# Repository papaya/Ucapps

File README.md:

# Ucapps
 Midibox files PCB kicad

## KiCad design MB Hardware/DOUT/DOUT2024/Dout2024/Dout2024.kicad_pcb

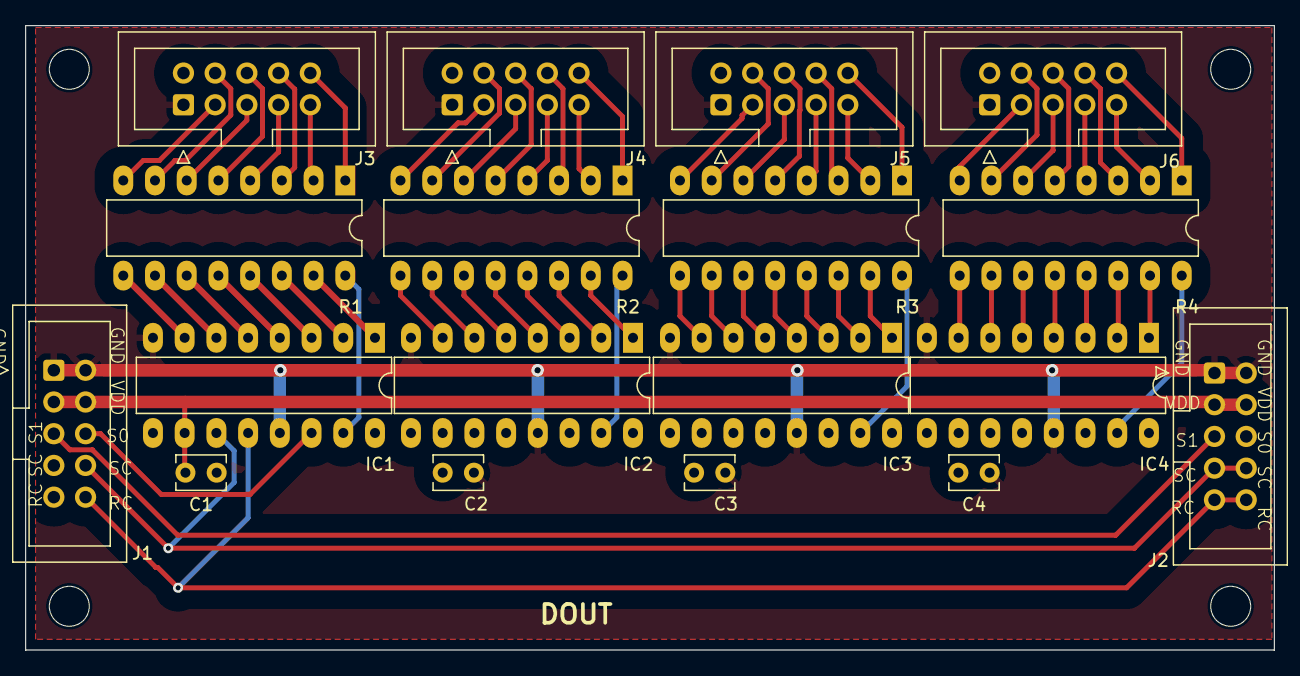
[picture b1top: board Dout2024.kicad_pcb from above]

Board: 2 copper layers, 100.0 x 50.0 mm, 22 parts (0 on the bottom side), 74 nets.

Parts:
C1, C2, C3, C4: 100NF; C_Disc_D3.8mm_W2.6mm_P2.50mm
H1, H2, H3, H4: MountingHole; MountingHole_3.2mm_M3
IC1, IC2, IC3, IC4: SN74HC595N; DIP-16_74h595
J1, J2: sin_in; IDC-Header_2x05_P2.54mm_Vertical_ksr_TO_J8_J9
J3, J4, J5, J6: sin_in; IDC-Header_2x05_P2.54mm_Vertical
R1: 220 ohm; DIP-16_R220_network
R2, R3, R4: 220 ohm; DIP-16_W7.62mm_LongPads

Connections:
+5V: C1.2, C2.2, C3.2, C4.2, IC1.10 (~SRCLR), IC1.16 (VCC), IC2.10 (~SRCLR), IC2.16 (VCC), IC3.10 (~SRCLR), IC3.16 (VCC), IC4.10 (~SRCLR), IC4.16 (VCC), J1.3, J1.4, J2.3, J2.4
/DOUT_RC: IC1.12 (RCLK), IC2.12 (RCLK), IC3.12 (RCLK), IC4.12 (RCLK), J1.10, J2.9, J2.10
/DOUT_SC: IC1.11 (SRCLK), IC2.11 (SRCLK), IC3.11 (SRCLK), IC4.11 (SRCLK), J1.8, J2.7, J2.8
/S0: IC1.14 (SER), J1.6
GND: C1.1, C2.1, C3.1, C4.1, IC1.8 (GND), IC1.13 (~OE), IC2.8 (GND), IC2.13 (~OE), IC3.8 (GND), IC3.13 (~OE), IC4.8 (GND), IC4.13 (~OE), J1.1, J1.2, J2.1, J2.2, J3.1, J4.1, J5.1, J6.1
unnamed: IC1.15 (QA), R1.16 (R1.2)
unnamed: IC1.1 (QB), R1.15 (R2.2)
unnamed: IC1.2 (QC), R1.14 (R3.2)
unnamed: IC1.3 (QD), R1.13 (R4.2)
unnamed: IC1.4 (QE), R1.12 (R5.2)
unnamed: IC1.5 (QF), R1.11 (R6.2)
unnamed: IC1.6 (QG), R1.10 (R7.2)
unnamed: IC1.7 (QH_1), R1.9 (R8.2)
unnamed: IC1.9 (QH_2), IC2.14 (SER)
unnamed: IC2.15 (QA), R2.16 (R1.2)
unnamed: IC2.1 (QB), R2.15 (R2.2)
unnamed: IC2.2 (QC), R2.14 (R3.2)
unnamed: IC2.3 (QD), R2.13 (R4.2)
unnamed: IC2.4 (QE), R2.12 (R5.2)
unnamed: IC2.5 (QF), R2.11 (R6.2)
unnamed: IC2.6 (QG), R2.10 (R7.2)
unnamed: IC2.7 (QH_1), R2.9 (R8.2)
unnamed: IC2.9 (QH_2), IC3.14 (SER)
unnamed: IC3.15 (QA), R3.16 (R1.2)
unnamed: IC3.1 (QB), R3.15 (R2.2)
unnamed: IC3.2 (QC), R3.14 (R3.2)
unnamed: IC3.3 (QD), R3.13 (R4.2)
unnamed: IC3.4 (QE), R3.12 (R5.2)
unnamed: IC3.5 (QF), R3.11 (R6.2)
unnamed: IC3.6 (QG), R3.10 (R7.2)
unnamed: IC3.7 (QH_1), R3.9 (R8.2)
unnamed: IC3.9 (QH_2), IC4.14 (SER)
unnamed: IC4.15 (QA), R4.16 (R1.2)
unnamed: IC4.1 (QB), R4.15 (R2.2)
unnamed: IC4.2 (QC), R4.14 (R3.2)
unnamed: IC4.3 (QD), R4.13 (R4.2)
unnamed: IC4.4 (QE), R4.12 (R5.2)
unnamed: IC4.5 (QF), R4.11 (R6.2)
unnamed: IC4.6 (QG), R4.10 (R7.2)
unnamed: IC4.7 (QH_1), R4.9 (R8.2)
unnamed: IC4.9 (QH_2), J2.6
unnamed: J1.5, J2.5
unnamed: J3.10, R1.1 (R1.1)
unnamed: J3.9, R1.2 (R2.1)
unnamed: J3.8, R1.3 (R3.1)
unnamed: J3.7, R1.4 (R4.1)
unnamed: J3.6, R1.5 (R5.1)
unnamed: J3.5, R1.6 (R6.1)
unnamed: J3.4, R1.7 (R7.1)
unnamed: J3.3, R1.8 (R8.1)
unnamed: J4.10, R2.1 (R1.1)
unnamed: J4.9, R2.2 (R2.1)
unnamed: J4.8, R2.3 (R3.1)
unnamed: J4.7, R2.4 (R4.1)
unnamed: J4.6, R2.5 (R5.1)
unnamed: J4.5, R2.6 (R6.1)
unnamed: J4.4, R2.7 (R7.1)
unnamed: J4.3, R2.8 (R8.1)
unnamed: J5.10, R3.1 (R1.1)
unnamed: J5.9, R3.2 (R2.1)
unnamed: J5.8, R3.3 (R3.1)
unnamed: J5.7, R3.4 (R4.1)
unnamed: J5.6, R3.5 (R5.1)
unnamed: J5.5, R3.6 (R6.1)
unnamed: J5.4, R3.7 (R7.1)
unnamed: J5.3, R3.8 (R8.1)
unnamed: J6.10, R4.1 (R1.1)
unnamed: J6.9, R4.2 (R2.1)
unnamed: J6.8, R4.3 (R3.1)
unnamed: J6.7, R4.4 (R4.1)
unnamed: J6.6, R4.5 (R5.1)
unnamed: J6.5, R4.6 (R6.1)
unnamed: J6.4, R4.7 (R7.1)
unnamed: J6.3, R4.8 (R8.1)

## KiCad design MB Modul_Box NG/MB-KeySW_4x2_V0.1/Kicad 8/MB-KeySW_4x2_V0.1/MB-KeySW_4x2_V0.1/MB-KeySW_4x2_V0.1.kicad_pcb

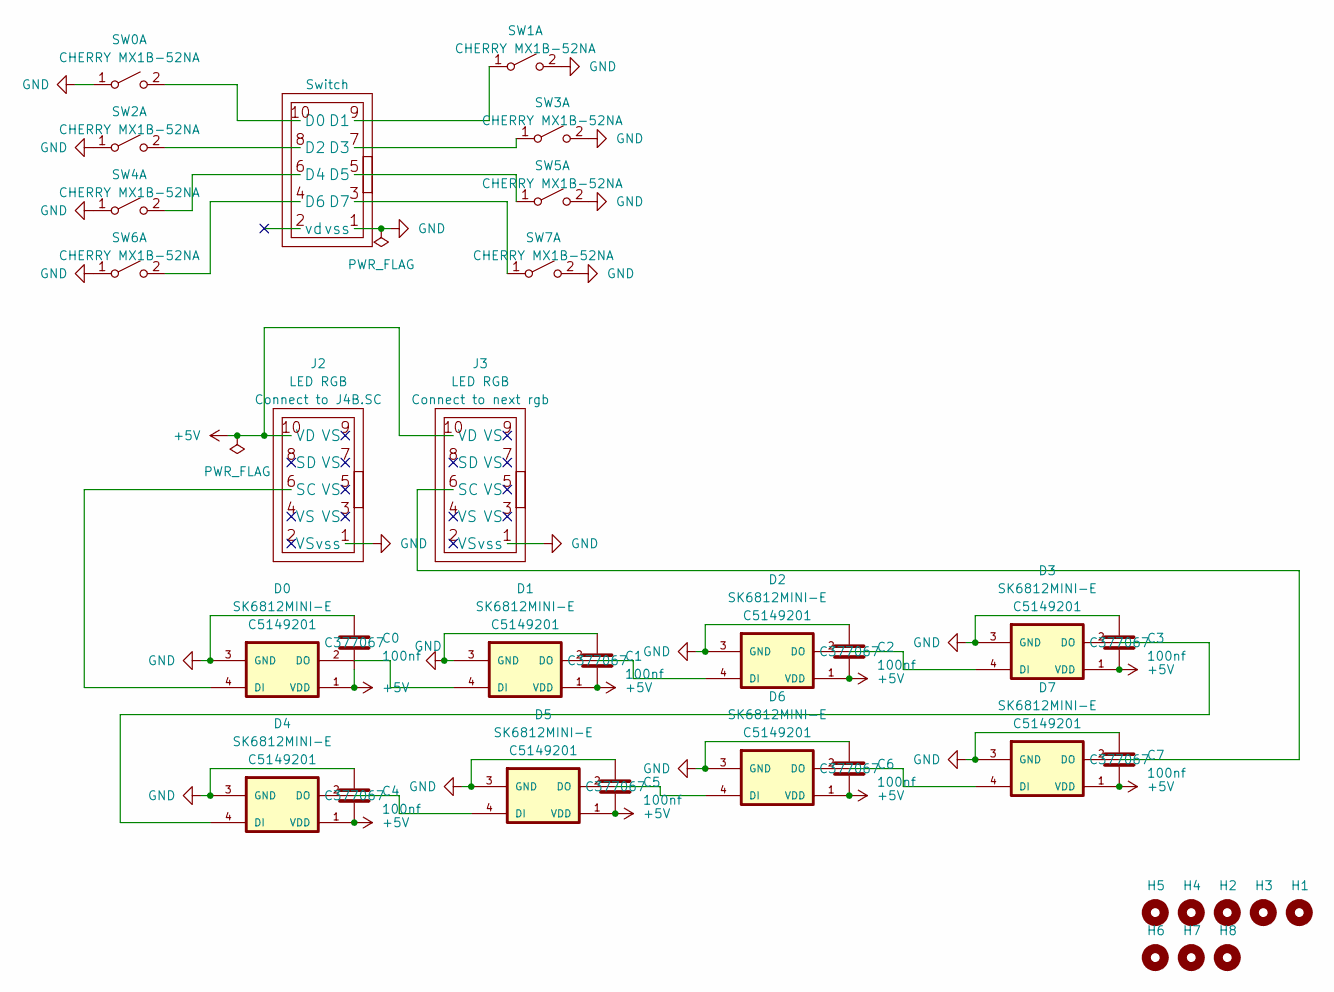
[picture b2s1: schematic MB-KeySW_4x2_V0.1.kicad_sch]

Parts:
C0, C1, C2, C3, C4, C5, C6, C7: 100nf; C_1206_3216Metric; JLCPCB Part # C377067
D0, D1, D2, D3, D4, D5, D6, D7: SK6812MINI-E; SK6812-MINI-E; JLCPCB Part # C5149201
H1, H2, H3, H4, H5, H6, H7, H8: MountingHole; MountingHole_3mm
J1, J2, J3: IDC-Header_2x05_P2.54mm_Vertical
SW0, SW1, SW2, SW3, SW4, SW5, SW6, SW7: CHERRY MX1B-52NA; SW_Alps_Matias_1.00u_cherry_LP

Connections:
+5V: C0.2, C1.2, C2.2, C3.2, C4.2, C5.2, C6.2, C7.2, D0.1 (VDD), D1.1 (VDD), D2.1 (VDD), D3.1 (VDD), D4.1 (VDD), D5.1 (VDD), D6.1 (VDD), D7.1 (VDD), J2.10 (VD), J3.10 (VD)
GND: C0.1, C1.1, C2.1, C3.1, C4.1, C5.1, C6.1, C7.1, D0.3 (GND), D1.3 (GND), D2.3 (GND), D3.3 (GND), D4.3 (GND), D5.3 (GND), D6.3 (GND), D7.3 (GND), J1.1 (vss), J2.1 (vss), J3.1 (vss), SW0.1 (A), SW1.2 (B), SW2.1 (A), SW3.2 (B), SW4.1 (A), SW5.2 (B), SW6.1 (A), SW7.2 (B)
unnamed: D0.2 (DO), D1.4 (DI)
unnamed: D0.4 (DI), J2.6 (SC)
unnamed: D1.2 (DO), D2.4 (DI)
unnamed: D2.2 (DO), D3.4 (DI)
unnamed: D3.2 (DO), D4.4 (DI)
unnamed: D4.2 (DO), D5.4 (DI)
unnamed: D5.2 (DO), D6.4 (DI)
unnamed: D6.2 (DO), D7.4 (DI)
unnamed: D7.2 (DO), J3.6 (SC)
unnamed: J1.10 (D0), SW0.2 (B)
unnamed: J1.9 (D1), SW1.1 (A)
unnamed: J1.8 (D2), SW2.2 (B)
unnamed: J1.7 (D3), SW3.1 (A)
unnamed: J1.6 (D4), SW4.2 (B)
unnamed: J1.5 (D5), SW5.1 (A)
unnamed: J1.4 (D6), SW6.2 (B)
unnamed: J1.3 (D7), SW7.1 (A)

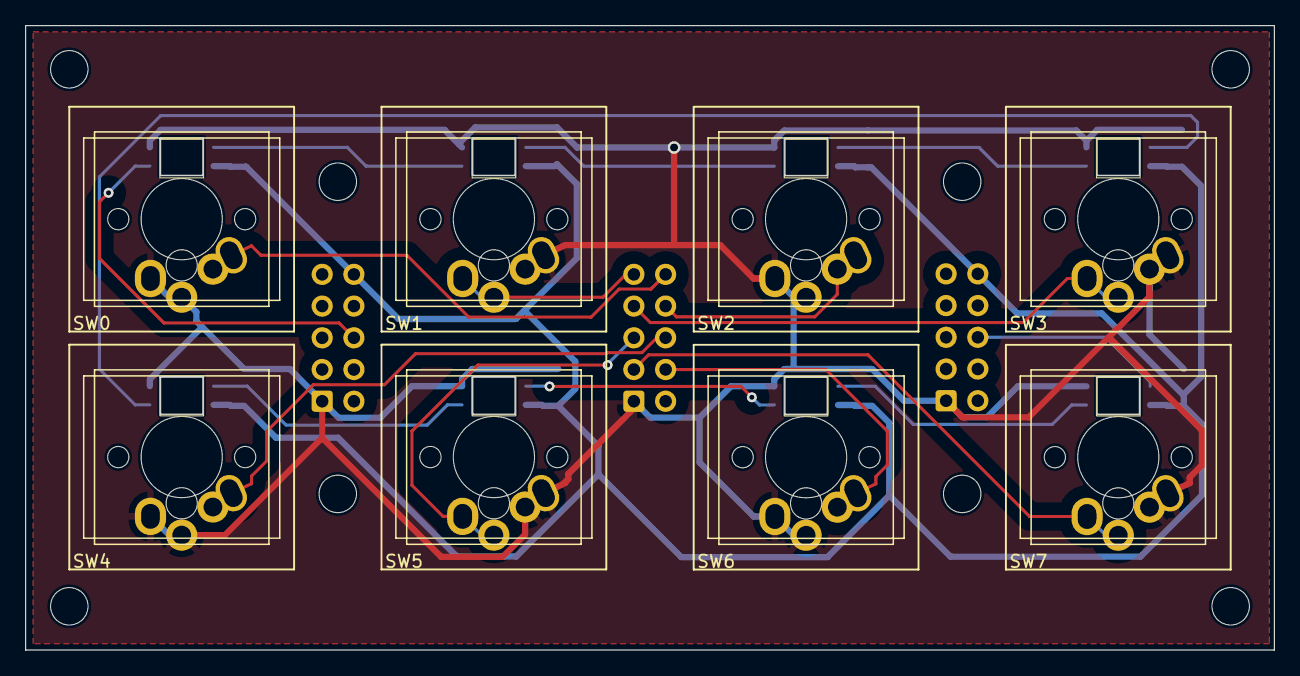
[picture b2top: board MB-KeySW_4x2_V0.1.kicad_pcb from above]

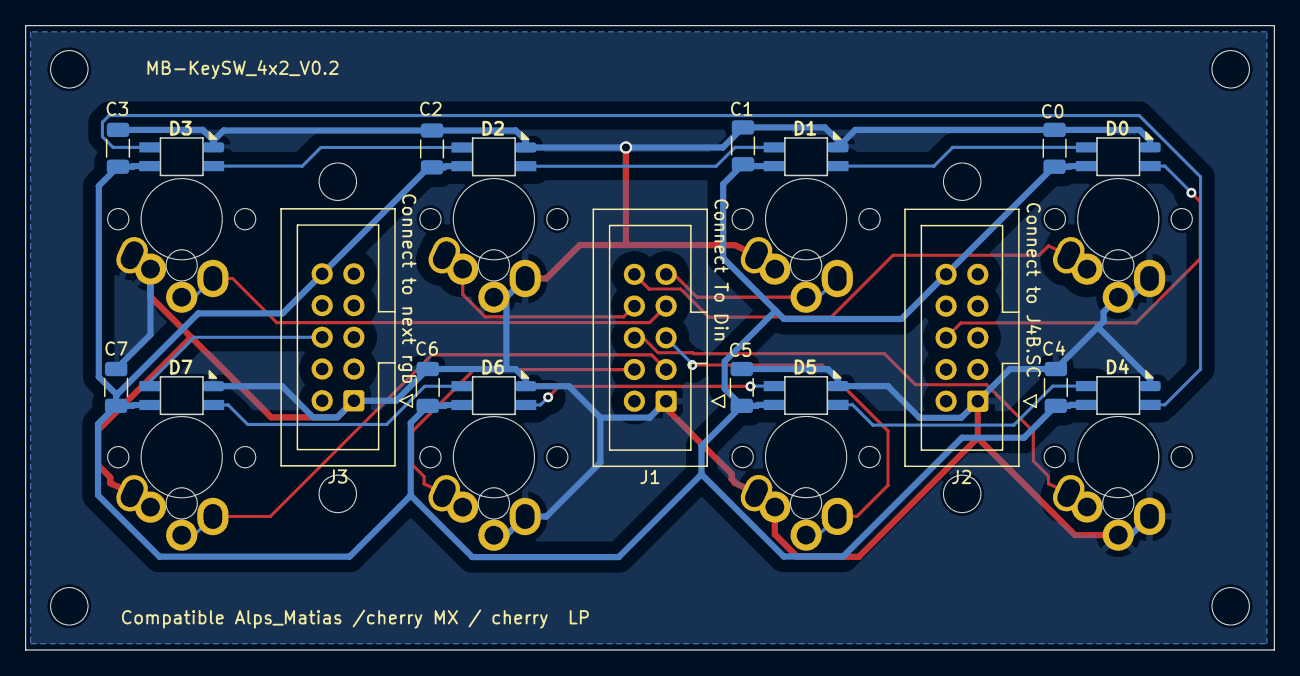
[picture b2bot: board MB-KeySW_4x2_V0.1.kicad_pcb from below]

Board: 2 copper layers, 100.0 x 50.0 mm, 35 parts (19 on the bottom side), 19 nets.

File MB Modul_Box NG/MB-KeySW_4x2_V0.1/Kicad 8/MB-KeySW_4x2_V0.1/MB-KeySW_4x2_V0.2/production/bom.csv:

Designator,Footprint,Quantity,Value,LCSC Part #
"C0, C1, C2, C3, C4, C5, C6, C7",1206,8,100nf,C377067
"D0, D1, D2, D3, D4, D5, D6, D7",SK6812-MINI-E,8,SK6812MINI-E,C5149201
"H1, H2, H3, H4, H5, H6, H7, H8",MountingHole_3mm,8,MountingHole,
"J1, J2, J3",IDC-Header_2x05_P2.54mm_Vertical,3,IDC-Header_2x05_P2.54mm_Vertical,
"SW0, SW1, SW2, SW3, SW4, SW5, SW6, SW7",SW_Alps_Matias_1.00u_cherry_LP,8,CHERRY MX1B-52NA,

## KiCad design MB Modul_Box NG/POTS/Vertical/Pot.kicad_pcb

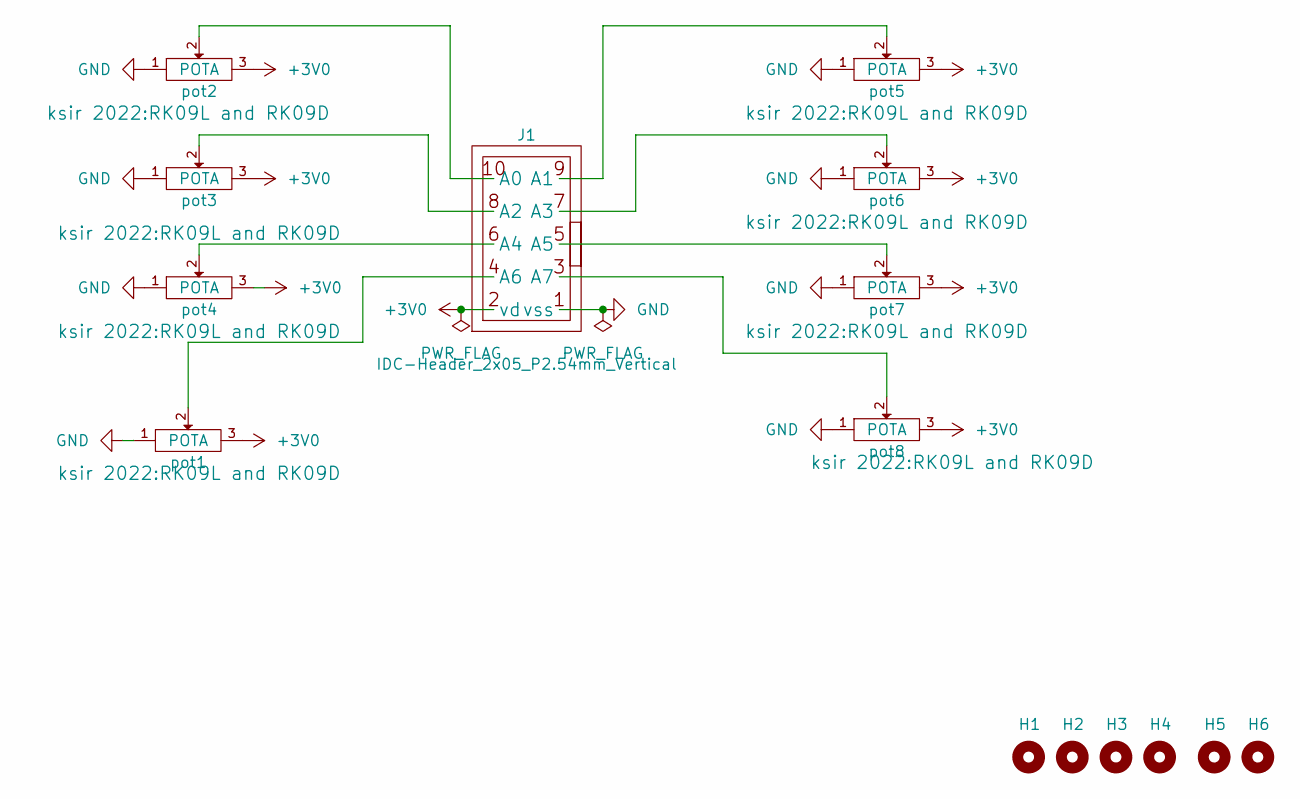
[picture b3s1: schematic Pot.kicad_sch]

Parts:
H1, H2, H3, H4, H5, H6: MountingHole; MountingHole_3.2mm_M3
J1: IDC-Header_2x05_P2.54mm_Vertical
pot1, pot2, pot3, pot4, pot5, pot6, pot7, pot8: POTA; RK09L and RK09D

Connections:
+3V0: J1.2 (vd), pot1.3 (vd), pot2.3 (vd), pot3.3 (vd), pot4.3 (vd), pot5.3 (vd), pot6.3 (vd), pot7.3 (vd), pot8.3 (vd)
GND: J1.1 (vss), pot1.1 (vss_masse), pot2.1 (vss_masse), pot3.1 (vss_masse), pot4.1 (vss_masse), pot5.1 (vss_masse), pot6.1 (vss_masse), pot7.1 (vss_masse), pot8.1 (vss_masse)
unnamed: J1.10 (A0), pot2.2
unnamed: J1.9 (A1), pot5.2
unnamed: J1.8 (A2), pot3.2
unnamed: J1.7 (A3), pot6.2
unnamed: J1.6 (A4), pot4.2
unnamed: J1.5 (A5), pot7.2
unnamed: J1.4 (A6), pot1.2
unnamed: J1.3 (A7), pot8.2

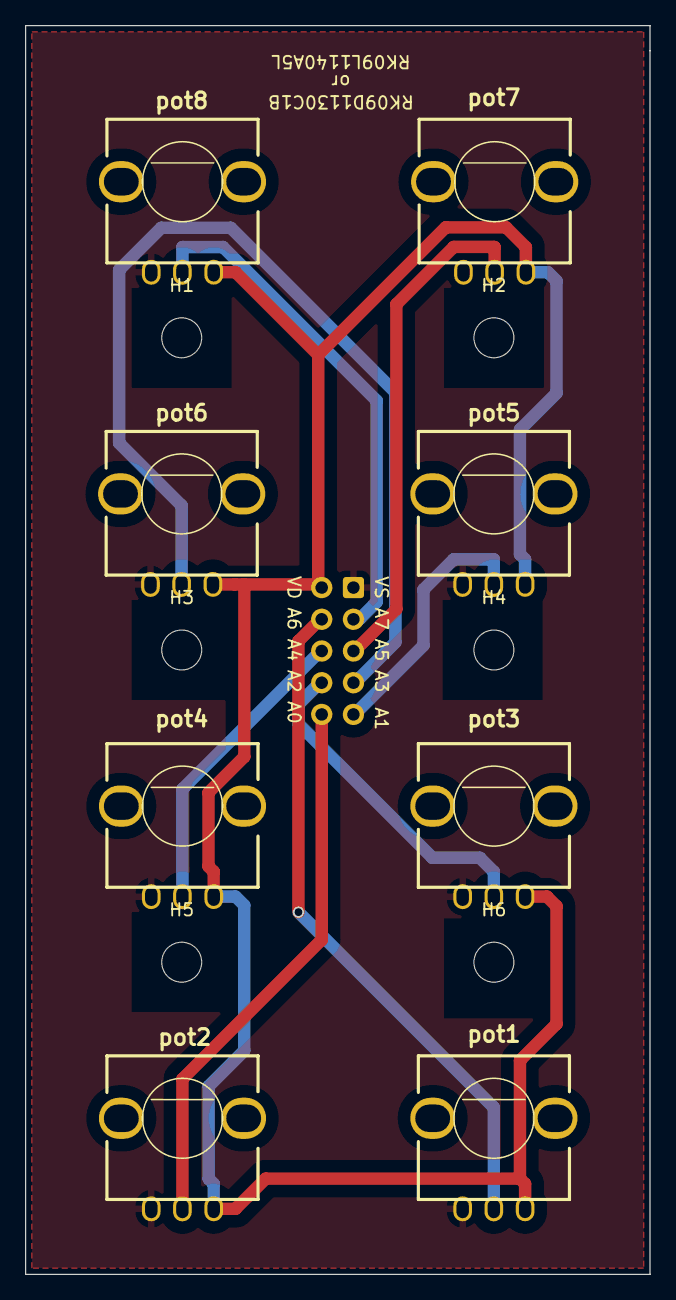
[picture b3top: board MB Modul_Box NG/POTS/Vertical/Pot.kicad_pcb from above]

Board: 2 copper layers, 50.0 x 100.0 mm, 15 parts (1 on the bottom side), 10 nets.

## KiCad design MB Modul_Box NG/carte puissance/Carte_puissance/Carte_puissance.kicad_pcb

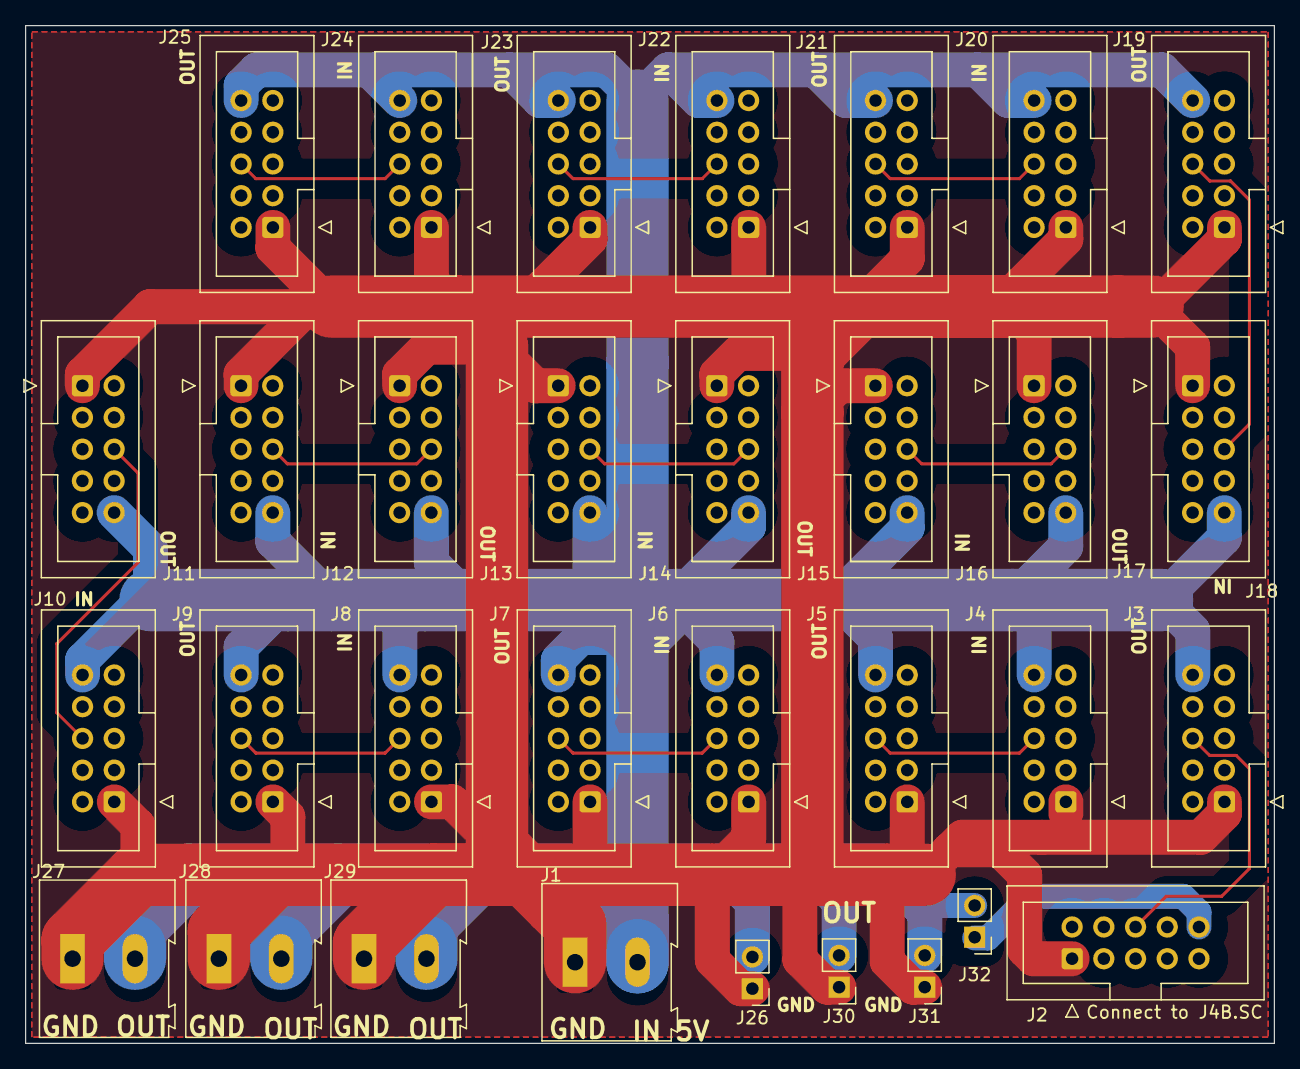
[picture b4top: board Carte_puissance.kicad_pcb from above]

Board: 2 copper layers, 100.0 x 81.5 mm, 32 parts (0 on the bottom side), 15 nets.

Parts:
J1, J28, J29: Input; TerminalBlock_Altech_AK300-2_P5.00mm
J2, J3, J4, J5, J6, J7, J8, J9, J10, J11, J12, J13, J14, J15, J16, J17, J18, J19, J20, J21, J22, J23, J24, J25: IDC-Header_2x05_P2.54mm_Vertical
J26, J30, J31: Input; PinHeader_1x02_P2.54mm_Vertical
J27: Output; TerminalBlock_Altech_AK300-2_P5.00mm
J32: Disconect; PinHeader_1x02_P2.54mm_Vertical

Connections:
+5VA: J2.10, J32.1
+5VD: J1.2, J3.10, J4.10, J5.10, J6.10, J7.10, J8.10, J9.10, J10.10, J11.10, J12.10, J13.10, J14.10, J15.10, J16.10, J17.10, J18.10, J19.10, J20.10, J21.10, J22.10, J23.10, J24.10, J25.10, J26.2, J27.2, J28.2, J29.2, J30.2, J31.2, J32.2
GNDA: J1.1, J2.1, J3.1, J4.1, J5.1, J6.1, J7.1, J8.1, J9.1, J10.1, J11.1, J12.1, J13.1, J14.1, J15.1, J16.1, J17.1, J18.1, J19.1, J20.1, J21.1, J22.1, J23.1, J24.1, J25.1, J26.1, J27.1, J28.1, J29.1, J30.1, J31.1
unnamed: J2.6, J3.6
unnamed: J4.6, J5.6
unnamed: J6.6, J7.6
unnamed: J8.6, J9.6
unnamed: J10.6, J11.6
unnamed: J12.6, J13.6
unnamed: J14.6, J15.6
unnamed: J16.6, J17.6
unnamed: J18.6, J19.6
unnamed: J20.6, J21.6
unnamed: J22.6, J23.6
unnamed: J24.6, J25.6

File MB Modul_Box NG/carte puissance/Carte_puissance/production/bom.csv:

Designator,Footprint,Quantity,Value,LCSC Part #
"J1, J28, J29",TerminalBlock_Altech_AK300-2_P5.00mm,3,Input,
"J10, J11, J12, J13, J14, J15, J16, J17, J18, J19, J2, J20, J21, J22, J23, J24, J25, J3, J4, J5, J6, J7, J8, J9",IDC-Header_2x05_P2.54mm_Vertical,24,IDC-Header_2x05_P2.54mm_Vertical,
"J26, J30, J31",PinHeader_1x02_P2.54mm_Vertical,3,Input,
J27,TerminalBlock_Altech_AK300-2_P5.00mm,1,Output,
J32,PinHeader_1x02_P2.54mm_Vertical,1,Disconect,

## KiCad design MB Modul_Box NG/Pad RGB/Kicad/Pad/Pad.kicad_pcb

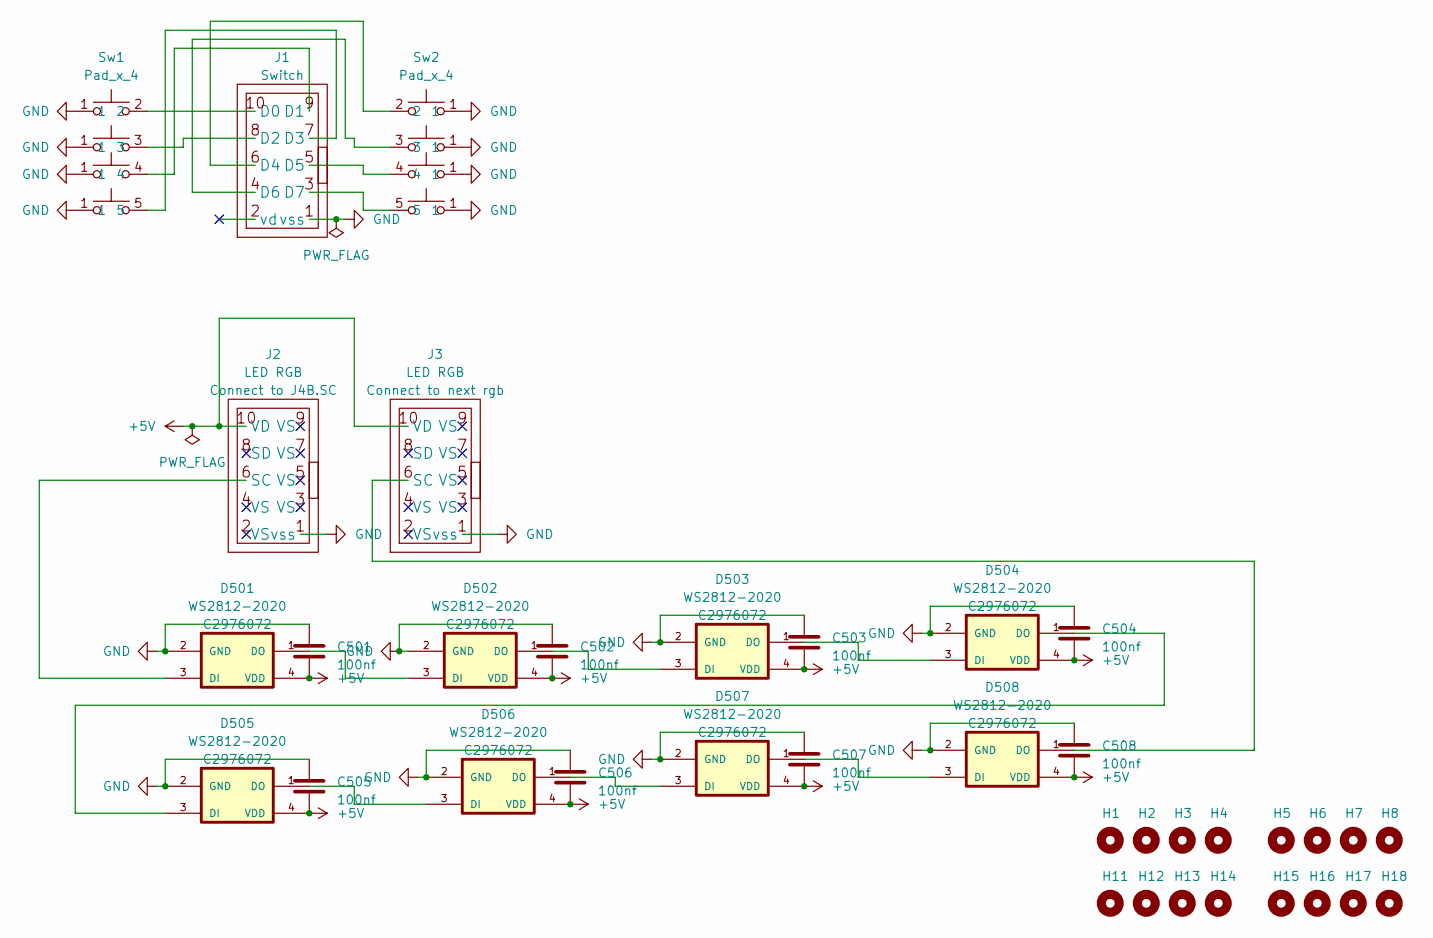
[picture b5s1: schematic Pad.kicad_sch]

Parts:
C501: 100nf; C_0402_1005Metric; JLCPCB Part # C1525
C502, C503, C504, C505, C506, C507, C508: 100nf; CAPC1005X55N; JLCPCB Part # C1525
D501, D502, D503, D504, D505, D506, D507, D508: WS2812-2020; LED_WS2812B-2020_PLCC4_2.0x2.0mm; JLCPCB Part # C2976072
H1, H2, H3, H4, H5, H6, H7, H8: MountingHole; MountingHole_2.2mm_M2
H11, H12, H13, H14, H15, H16, H17, H18: MountingHole; MountingHole_3mm
J1, J2, J3: IDC-Header_2x05_P2.54mm_Vertical
Sw1, Sw2: Pad_x_4; Pad x 4

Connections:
+5V: C501.2, C502.2, C503.2, C504.2, C505.2, C506.2, C507.2, C508.2, D501.4 (VDD), D502.4 (VDD), D503.4 (VDD), D504.4 (VDD), D505.4 (VDD), D506.4 (VDD), D507.4 (VDD), D508.4 (VDD), J2.10 (VD), J3.10 (VD)
GND: C501.1, C502.1, C503.1, C504.1, C505.1, C506.1, C507.1, C508.1, D501.2 (GND), D502.2 (GND), D503.2 (GND), D504.2 (GND), D505.2 (GND), D506.2 (GND), D507.2 (GND), D508.2 (GND), J1.1 (vss), J2.1 (vss), J3.1 (vss), Sw1.1, Sw2.1
unnamed: D501.3 (DI), J2.6 (SC)
unnamed: D501.1 (DO), D502.3 (DI)
unnamed: D502.1 (DO), D503.3 (DI)
unnamed: D503.1 (DO), D504.3 (DI)
unnamed: D504.1 (DO), D505.3 (DI)
unnamed: D505.1 (DO), D506.3 (DI)
unnamed: D506.1 (DO), D507.3 (DI)
unnamed: D507.1 (DO), D508.3 (DI)
unnamed: D508.1 (DO), J3.6 (SC)
unnamed: J1.10 (D0), Sw1.2
unnamed: J1.9 (D1), Sw1.4
unnamed: J1.8 (D2), Sw1.3
unnamed: J1.7 (D3), Sw1.5
unnamed: J1.6 (D4), Sw2.2
unnamed: J1.5 (D5), Sw2.4
unnamed: J1.4 (D6), Sw2.3
unnamed: J1.3 (D7), Sw2.5

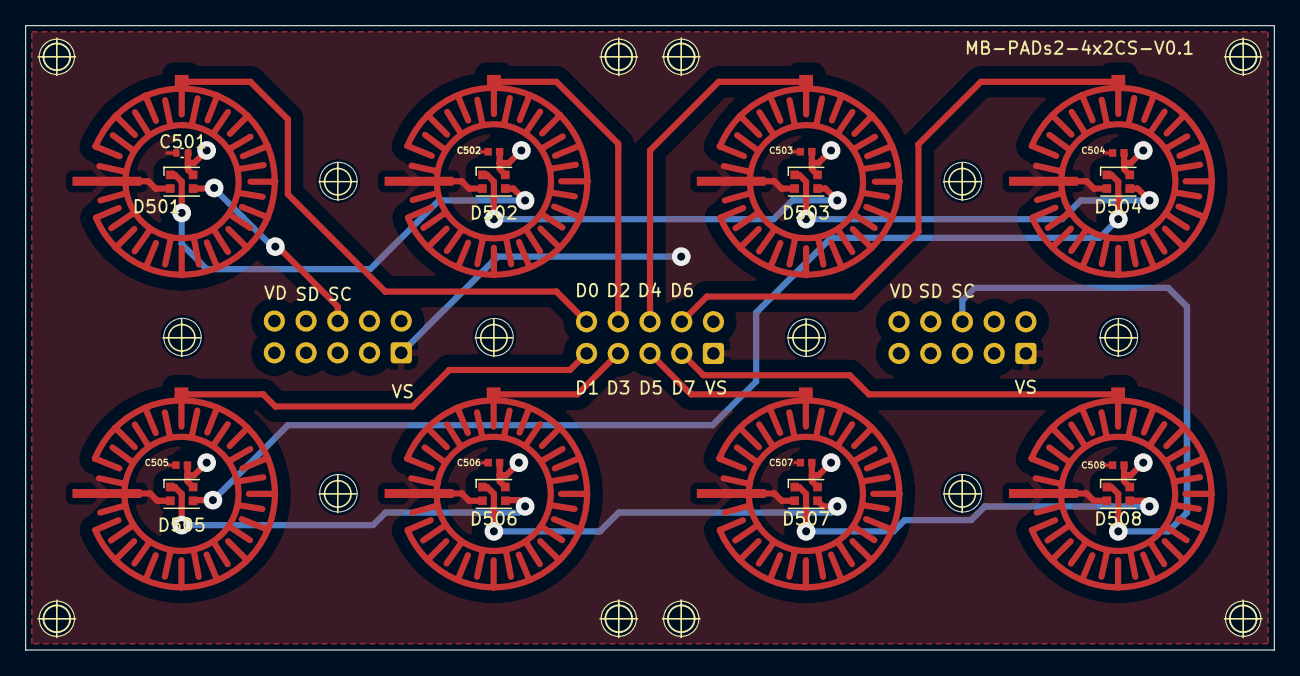
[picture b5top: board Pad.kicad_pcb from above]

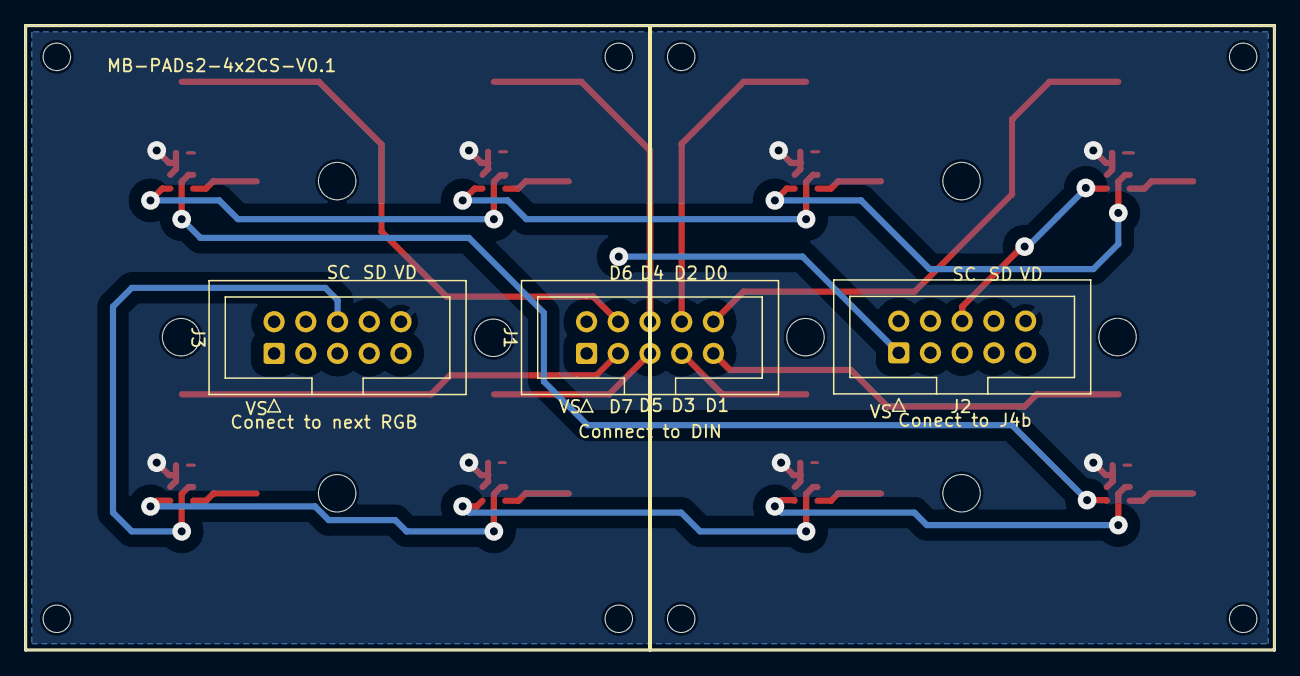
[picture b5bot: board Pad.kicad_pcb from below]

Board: 2 copper layers, 100.0 x 50.0 mm, 37 parts (3 on the bottom side), 19 nets.

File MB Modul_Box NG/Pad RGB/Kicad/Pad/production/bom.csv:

Designator,Footprint,Quantity,Value,LCSC Part #
C501,0402,1,100nf,C1525
"C502, C503, C504, C505, C506, C507, C508",CAPC1005X55N,7,100nf,C1525
"D501, D502, D503, D504, D505, D506, D507, D508",LED_WS2812B-2020_PLCC4_2.0x2.0mm,8,WS2812-2020,C2976072
"H1, H2, H3, H4, H5, H6, H7, H8",MountingHole_2.2mm_M2,8,MountingHole,
"H11, H12, H13, H14, H15, H16, H17, H18",MountingHole_3mm,8,MountingHole,
"J1, J2, J3",IDC-Header_2x05_P2.54mm_Vertical,3,IDC-Header_2x05_P2.54mm_Vertical,
"Sw1, Sw2",Pad x 4,2,Pad_x_4,

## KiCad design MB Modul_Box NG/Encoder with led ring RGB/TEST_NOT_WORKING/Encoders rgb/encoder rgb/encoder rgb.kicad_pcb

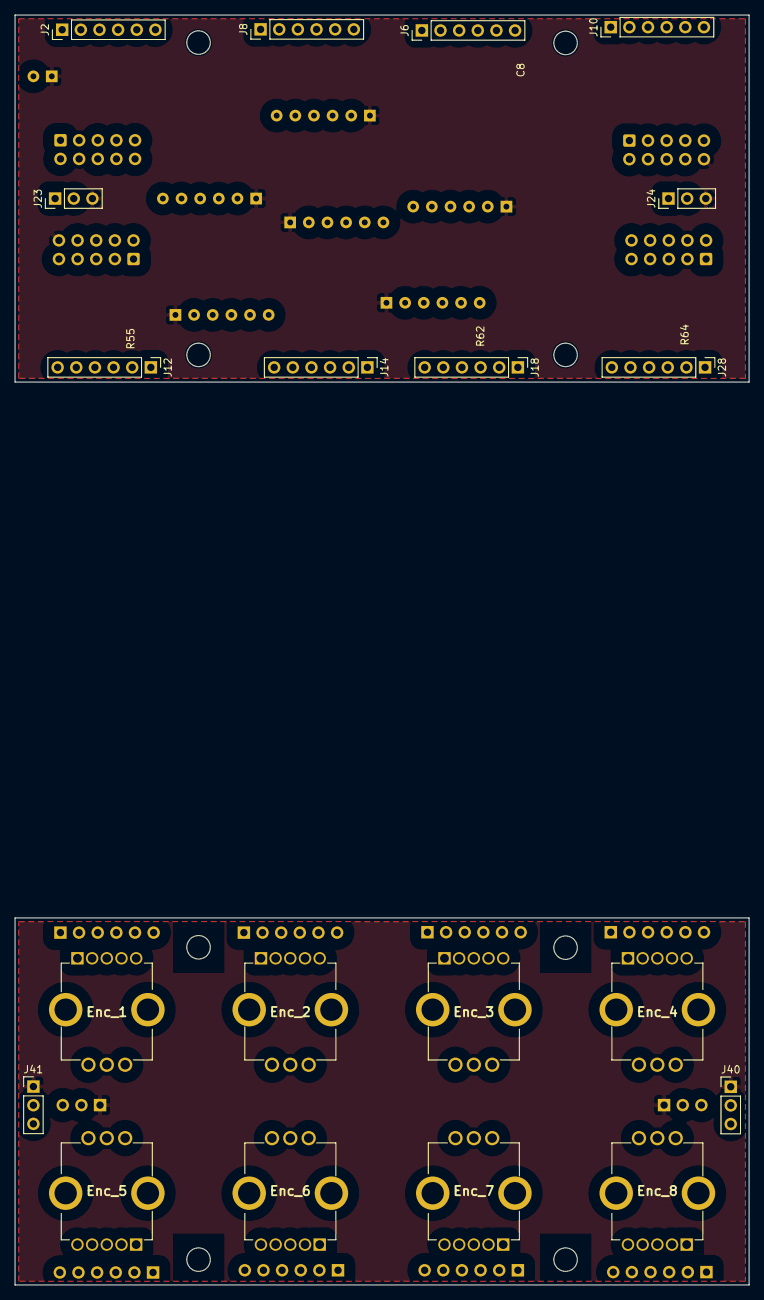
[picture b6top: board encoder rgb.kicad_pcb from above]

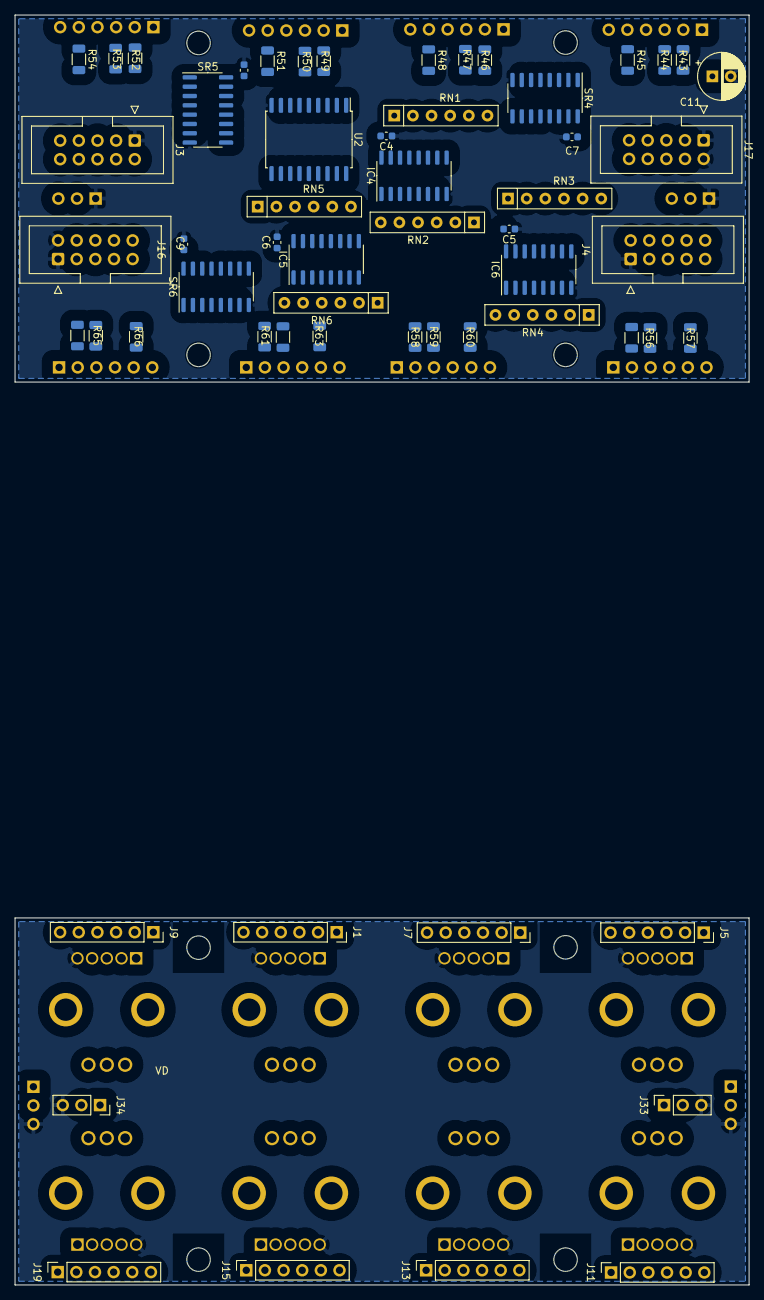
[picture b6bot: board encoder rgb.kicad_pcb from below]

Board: 2 copper layers, 100.0 x 173.0 mm, 86 parts (58 on the bottom side), 148 nets, no tracks yet.

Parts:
C4, C5, C6, C7, C8, C9: 100NF; C_0603_1608Metric
C11: 100UF; CP_Radial_D6.3mm_P2.50mm
Enc_1, Enc_2, Enc_3, Enc_4, Enc_5, Enc_6, Enc_7, Enc_8: PEL12T-4226F-S1024; PEL12T4226FS1024
H1, H2, H3, H4, H5, H6, H7, H8: MountingHole; MountingHole_3.2mm_M3
IC4, IC5, IC6: 74HC165; SOIC-16_3.9x9.9mm_P1.27mm
J1, J5, J7, J9, J11, J13, J15, J19: Conn_01x06_Socket; PinSocket_1x06_P2.54mm_Vertical
J2, J6, J8, J10, J12, J14, J18, J28: Conn_01x06_Pin; PinHeader_1x06_P2.54mm_Vertical
J3, J4: IDC-Header_2x05_P2.54mm_Vertical
J16, J17: sin_in; IDC-Header_2x05_P2.54mm_Vertical
J23, J24, J40, J41: Conn_01x03_Pin; PinHeader_1x03_P2.54mm_Vertical
J33, J34: Conn_01x03_Socket; PinSocket_1x03_P2.54mm_Vertical
R43, R44, R45, R46, R47, R48, R49, R50, R51, R52, R53, R54, R55, R56, R57, R58, R59, R60, R61, R62, R63, R64, R65, R66: 220 ohm; R_1206_3216Metric
RN1, RN2, RN3, RN4, RN5, RN6: 10K; R_Array_SIP6
SR4, SR5, SR6: 74HC595; SOIC-16_3.9x9.9mm_P1.27mm
U2: ULN2803A; SOIC-18W_7.5x11.6mm_P1.27mm

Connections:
+5V: C4.2, C5.2, C6.2, C7.2, C8.2, C9.2, C11.1, IC4.16 (VCC), IC5.16 (VCC), IC6.16 (VCC), J3.10 (VD), J4.10 (VD), J16.3 (VS), J16.4 (VS), J17.3 (VS), J17.4 (VS), J23.3, J24.3, RN1.1 (common), RN2.1 (common), RN3.1 (common), RN4.1 (common), RN5.1 (common), RN6.1 (common), SR4.10 (~SRCLR), SR4.16 (VCC), SR5.10 (~SRCLR), SR5.16 (VCC), SR6.10 (~SRCLR), SR6.16 (VCC)
+5VA: Enc_1.5 (ANODE), Enc_2.5 (ANODE), Enc_3.5 (ANODE), Enc_4.5 (ANODE), Enc_5.5 (ANODE), Enc_6.5 (ANODE), Enc_7.5 (ANODE), Enc_8.5 (ANODE), J33.3, J34.3, J40.3, J41.3
Blue_1: J2.5, R45.1
Blue_2: J8.5, R48.1
Blue_3: J6.5, R51.1
Blue_4: J10.5, R54.1
Blue_5: J12.5, R57.1
Blue_6: J14.5, R60.1
Blue_7: J18.5, R63.1
Blue_8: J28.5, R66.1
C_ENC1A: IC4.12 (D1), J2.1, RN1.4 (R3)
C_ENC1B: IC4.11 (D0), J2.6, RN1.5 (R4)
C_ENC2A: IC4.14 (D3), J8.1, RN1.2 (R1)
C_ENC2B: IC4.13 (D2), J8.6, RN1.3 (R2)
C_ENC3A: IC4.4 (D5), J6.1, RN2.4 (R3)
C_ENC3B: IC4.3 (D4), J6.6, RN2.5 (R4)
C_ENC4A: IC4.6 (D7), J10.1, RN2.2 (R1)
C_ENC4B: IC4.5 (D6), J10.6, RN2.3 (R2)
C_ENC5A: IC6.12 (D1), J12.1, RN3.4 (R3)
C_ENC5B: IC6.11 (D0), J12.6, RN3.5 (R4)
C_ENC6A: IC6.14 (D3), J14.1, RN3.2 (R1)
C_ENC6B: IC6.13 (D2), J14.6, RN3.3 (R2)
C_ENC7A: IC6.4 (D5), J18.1, RN4.4 (R3)
C_ENC7B: IC6.3 (D4), J18.6, RN4.5 (R4)
C_ENC8A: IC6.6 (D7), J28.1, RN4.2 (R1)
C_ENC8B: IC6.5 (D6), J28.6, RN4.3 (R2)
C_SW1: J2.4, U2.1 (I1)
C_SW2: J8.4, U2.2 (I2)
C_SW3: J6.4, U2.3 (I3)
C_SW4: J10.4, U2.4 (I4)
C_SW5: J12.4, U2.5 (I5)
C_SW6: J14.4, U2.6 (I6)
C_SW7: J18.4, U2.7 (I7)
C_SW8: J28.4, U2.8 (I8)
DIN_RC: IC4.1 (~PL), IC5.1 (~PL), IC6.1 (~PL), J16.9 (VS), J17.9 (VS)
DIN_SC: IC4.2 (CP), IC5.2 (CP), IC6.2 (CP), J16.7 (VS), J17.7 (VS)
Dout_RC: J16.10 (VD), J17.10 (VD), SR4.12 (RCLK), SR5.12 (RCLK), SR6.12 (RCLK)
Dout_SC: J16.8 (SD), J17.8 (SD), SR4.11 (SRCLK), SR5.11 (SRCLK), SR6.11 (SRCLK)
ENC1A: Enc_1.A1 (INPUT), J5.1
ENC1B: Enc_1.B1 (OUTPUT), J5.6
ENC2A: Enc_2.A1 (INPUT), J7.1
ENC2B: Enc_2.B1 (OUTPUT), J7.6
ENC3A: Enc_3.A1 (INPUT), J1.1
ENC3B: Enc_3.B1 (OUTPUT), J1.6
ENC4A: Enc_4.A1 (INPUT), J9.1
ENC4B: Enc_4.B1 (OUTPUT), J9.6
ENC5A: Enc_5.A1 (INPUT), J11.1
ENC5B: Enc_5.B1 (OUTPUT), J11.6
ENC6A: Enc_6.A1 (INPUT), J13.1
ENC6B: Enc_6.B1 (OUTPUT), J13.6
ENC7A: Enc_7.A1 (INPUT), J15.1
ENC7B: Enc_7.B1 (OUTPUT), J15.6
ENC8A: Enc_8.A1 (INPUT), J19.1
ENC8B: Enc_8.B1 (OUTPUT), J19.6
ENC_Blue_1: Enc_1.4 (CATHODE_3), J5.5
ENC_Blue_2: Enc_2.4 (CATHODE_3), J7.5
ENC_Blue_3: Enc_3.4 (CATHODE_3), J1.5
ENC_Blue_4: Enc_4.4 (CATHODE_3), J9.5
ENC_Blue_5: Enc_5.4 (CATHODE_3), J11.5
ENC_Blue_6: Enc_6.4 (CATHODE_3), J13.5
ENC_Blue_7: Enc_7.4 (CATHODE_3), J15.5
ENC_Blue_8: Enc_8.4 (CATHODE_3), J19.5
ENC_Green_1: Enc_1.2 (CATHODE_2), J5.3
ENC_Green_2: Enc_2.2 (CATHODE_2), J7.3
ENC_Green_3: Enc_3.2 (CATHODE_2), J1.3
ENC_Green_4: Enc_4.2 (CATHODE_2), J9.3
ENC_Green_5: Enc_5.2 (CATHODE_2), J11.3
ENC_Green_6: Enc_6.2 (CATHODE_2), J13.3
ENC_Green_7: Enc_7.2 (CATHODE_2), J15.3
ENC_Green_8: Enc_8.2 (CATHODE_2), J19.3
ENC_Red_1: Enc_1.1 (CATHODE_1), J5.2
ENC_Red_2: Enc_2.1 (CATHODE_1), J7.2
ENC_Red_3: Enc_3.1 (CATHODE_1), J1.2
ENC_Red_4: Enc_4.1 (CATHODE_1), J9.2
ENC_Red_5: Enc_5.1 (CATHODE_1), J11.2
ENC_Red_6: Enc_6.1 (CATHODE_1), J13.2
ENC_Red_7: Enc_7.1 (CATHODE_1), J15.2
ENC_Red_8: Enc_8.1 (CATHODE_1), J19.2
GND: C4.1, C5.1, C6.1, C7.1, C8.1, C9.1, C11.2, IC4.8 (GND), IC4.15 (~CE), IC5.8 (GND), IC5.15 (~CE), IC6.8 (GND), IC6.15 (~CE), J3.1 (vss), J4.1 (vss), J16.1 (vss), J16.2 (VS), J17.1 (vss), J17.2 (VS), J23.1, J24.1, SR4.8 (GND), SR4.13 (~OE), SR5.8 (GND), SR5.13 (~OE), SR6.8 (GND), SR6.13 (~OE), U2.9 (GND)
GND1: Enc_1.C1 (GND), Enc_2.C1 (GND), Enc_3.C1 (GND), Enc_4.C1 (GND), Enc_5.C1 (GND), Enc_6.C1 (GND), Enc_7.C1 (GND), Enc_8.C1 (GND), J33.1, J34.1, J40.1, J41.1
Green_1: J2.3, R44.1
Green_2: J8.3, R47.1
Green_3: J6.3, R50.1
Green_4: J10.3, R53.1
Green_5: J12.3, R56.1
Green_6: J14.3, R59.1
Green_7: J18.3, R62.1
Green_8: J28.3, R65.1
unnamed: IC4.10 (DS), IC6.9 (Q7), RN1.6 (R5)
unnamed: IC4.9 (Q7), J17.5 (VS)
unnamed: IC5.11 (D0), RN5.5 (R4), U2.18 (O1)
unnamed: IC5.12 (D1), RN5.4 (R3), U2.17 (O2)
unnamed: IC5.13 (D2), RN5.3 (R2), U2.16 (O3)
unnamed: IC5.14 (D3), RN5.2 (R1), U2.15 (O4)
unnamed: IC5.3 (D4), RN6.5 (R4), U2.14 (O5)
unnamed: IC5.4 (D5), RN6.4 (R3), U2.13 (O6)
unnamed: IC5.5 (D6), RN6.3 (R2), U2.12 (O7)
unnamed: IC5.6 (D7), RN6.2 (R1), U2.11 (O8)
unnamed: IC5.10 (DS), J16.5 (VS), RN5.6 (R5)
unnamed: IC5.9 (Q7), IC6.10 (DS), RN3.6 (R5)
unnamed: J4.6 (SC), J23.2
unnamed: J3.6 (SC), J24.2
unnamed: J33.2, J40.2
unnamed: J34.2, J41.2
unnamed: R43.2, SR4.15 (QA)
unnamed: R44.2, SR4.1 (QB)
unnamed: R45.2, SR4.2 (QC)
unnamed: R46.2, SR4.3 (QD)
unnamed: R47.2, SR4.4 (QE)
unnamed: R48.2, SR4.5 (QF)
unnamed: R49.2, SR4.6 (QG)
unnamed: R50.2, SR4.7 (QH)
unnamed: R51.2, SR5.15 (QA)
unnamed: R52.2, SR5.1 (QB)
unnamed: R53.2, SR5.2 (QC)
unnamed: R54.2, SR5.3 (QD)
unnamed: R55.2, SR5.4 (QE)
unnamed: R56.2, SR5.5 (QF)
unnamed: R57.2, SR5.6 (QG)
unnamed: R58.2, SR5.7 (QH)
unnamed: R59.2, SR6.15 (QA)
unnamed: R60.2, SR6.1 (QB)
unnamed: R61.2, SR6.2 (QC)
unnamed: R62.2, SR6.3 (QD)
unnamed: R63.2, SR6.4 (QE)
unnamed: R64.2, SR6.5 (QF)
unnamed: R65.2, SR6.6 (QG)
unnamed: R66.2, SR6.7 (QH)
Red_1: J2.2, R43.1
Red_2: J8.2, R46.1
Red_3: J6.2, R49.1
Red_4: J10.2, R52.1
Red_5: J12.2, R55.1
Red_6: J14.2, R58.1
Red_7: J18.2, R61.1
Red_8: J28.2, R64.1
SC1: J17.6 (SC), SR4.14 (SER)
SC2: SR4.9 (QH'), SR5.14 (SER)
SC3: SR5.9 (QH'), SR6.14 (SER)
SC4: J16.6 (SC), SR6.9 (QH')
SW1: Enc_1.3 (NO), J5.4
SW2: Enc_2.3 (NO), J7.4
SW3: Enc_3.3 (NO), J1.4
SW4: Enc_4.3 (NO), J9.4
SW5: Enc_5.3 (NO), J11.4
SW6: Enc_6.3 (NO), J13.4
SW7: Enc_7.3 (NO), J15.4
SW8: Enc_8.3 (NO), J19.4
